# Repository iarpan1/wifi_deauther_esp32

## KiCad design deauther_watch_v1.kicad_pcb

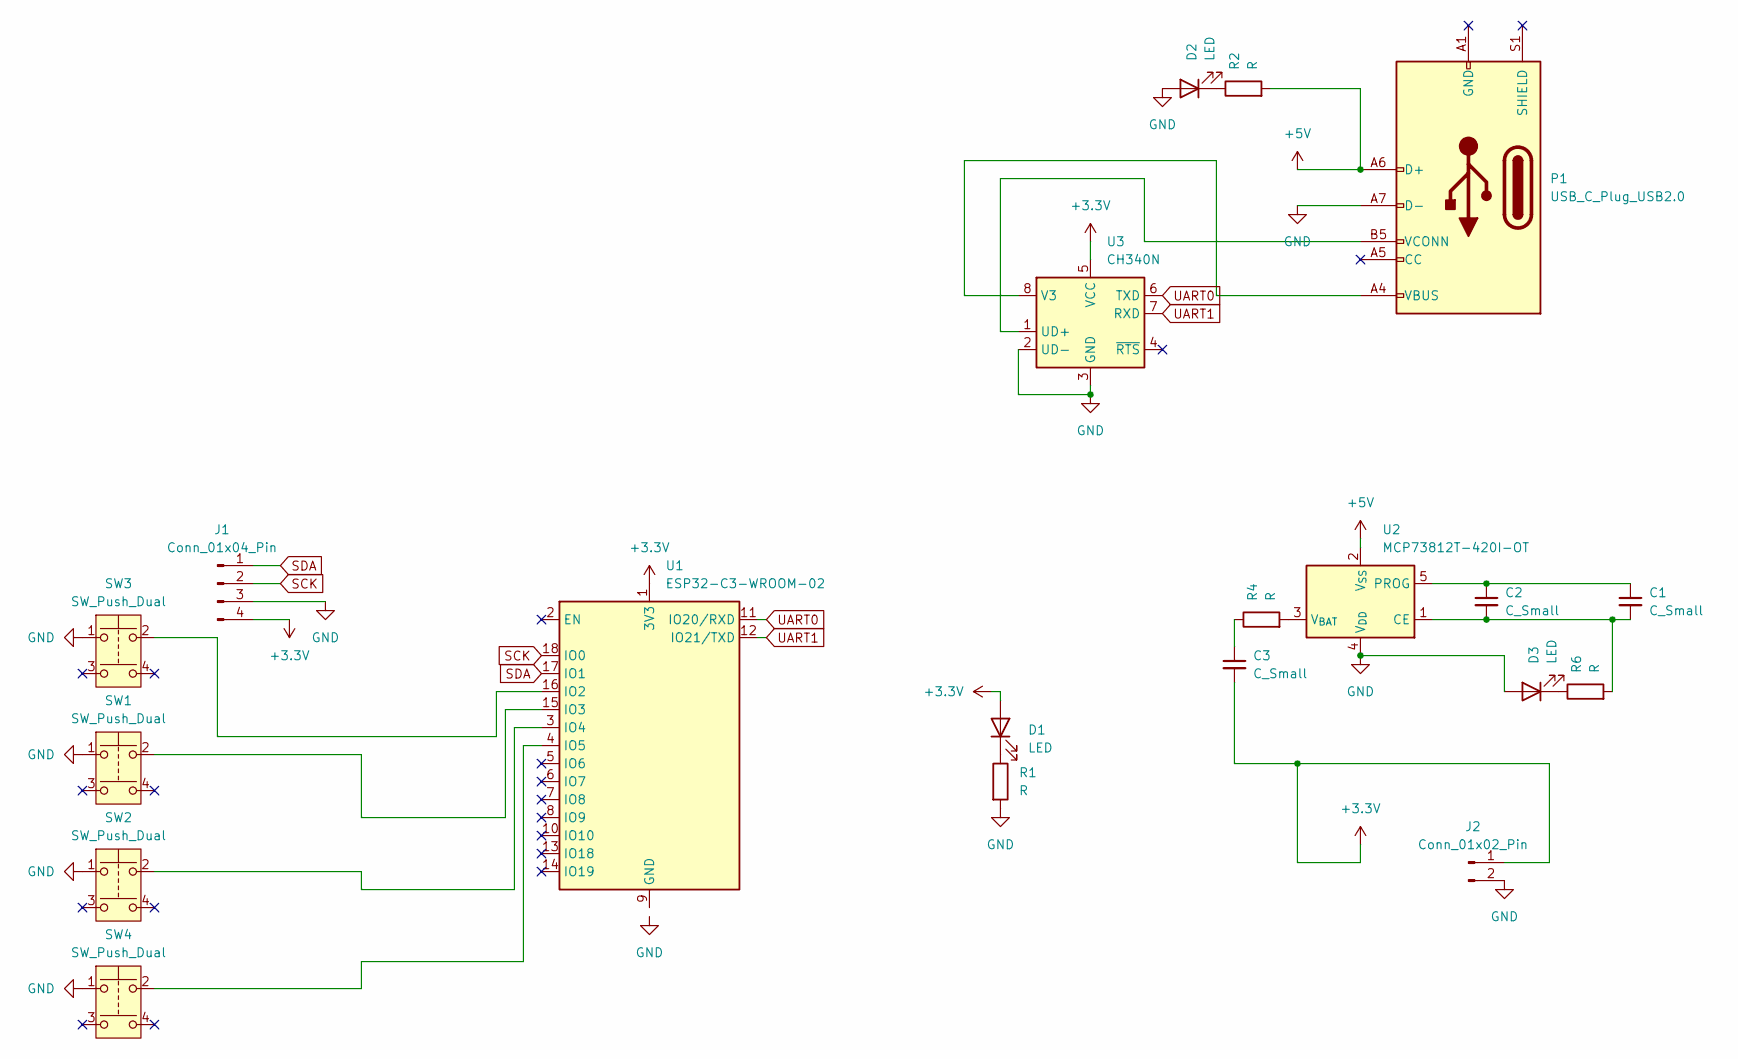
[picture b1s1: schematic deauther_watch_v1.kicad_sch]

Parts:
C1, C2, C3: C_Small; C_0603_1608Metric
D1, D2, D3: LED; LED_0402_1005Metric
J1: Conn_01x04_Pin; Harwin_M20-89004xx_1x04_P2.54mm_Horizontal
J2: Conn_01x02_Pin; JST_EH_S2B-EH_1x02_P2.50mm_Horizontal
P1: USB_C_Plug_USB2.0; USB_C_Plug_Molex_105444
R1, R2, R4, R6: R; R_0612_1632Metric_Pad1.18x3.40mm_HandSolder
SW1, SW2, SW3, SW4: SW_Push_Dual; SW_TH_Tactile_Omron_B3F-10xx
U1: ESP32-C3-WROOM-02
U2: MCP73812T-420I-OT; SOT-23-5
U3: CH340N; SOP-8_3.9x4.9mm_P1.27mm

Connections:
+3.3V: C3.2, D1.2 (A), J1.4, J2.1, U1.1 (3V3), U3.5 (VCC)
+5V: P1.A6 (D+), R2.2, U2.2 (V_{SS})
GND: D2.2 (A), D3.2 (A), J1.3, J2.2, P1.A7 (D-), R1.2, SW1.1, SW2.1, SW3.1, SW4.1, U2.4 (V_{DD}), U3.2 (UD-), U3.3 (GND)
unnamed: C3.1, R4.1
unnamed: D1.1 (K), R1.1
unnamed: D2.1 (K), R2.1
unnamed: D3.1 (K), R6.1
unnamed: P1.B5 (VCONN), U3.1 (UD+)
unnamed: U1.9 (GND), U1.19 (GND)
unnamed: SW3.2, U1.16 (IO2)
unnamed: SW1.2, U1.15 (IO3)
unnamed: SW2.2, U1.3 (IO4)
unnamed: SW4.2, U1.4 (IO5)
unnamed: C1.2, C2.2, R6.2, U2.1 (CE)
unnamed: C1.1, C2.1, U2.5 (PROG)
unnamed: R4.2, U2.3 (V_{BAT})
unnamed: P1.A4 (VBUS), P1.A9 (VBUS), P1.B4 (VBUS), P1.B9 (VBUS), U3.8 (V3)
SCK: J1.2, U1.18 (IO0)
SDA: J1.1, U1.17 (IO1)
UART0: U1.11 (IO20/RXD), U3.6 (TXD)
UART1: U1.12 (IO21/TXD), U3.7 (RXD)

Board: 2 copper layers, 20 parts (0 on the bottom side), 21 nets, no tracks yet.
